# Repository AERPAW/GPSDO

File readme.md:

# AERPAW GPSDO

This repository contains the firmware, host utilities and design files for the AERPAW GPSDO.

The firmware is available in `firmware/` and the status utility in `gpsdo_status/`. See the readme in each for more information.

Install `gpsdo_cli` on Linux:

```sh
curl -fsSL https://raw.githubusercontent.com/AERPAW/GPSDO/main/gpsdo_cli/gpsdo_cli.py | sudo install -m 0755 /dev/stdin /usr/local/bin/gpsdo_cli
```

If `gpsdo_cli` cannot access `/dev/ttyACM*`, add your user to the serial device group and log out/in:

```sh
sudo usermod -aG dialout "$USER"
```

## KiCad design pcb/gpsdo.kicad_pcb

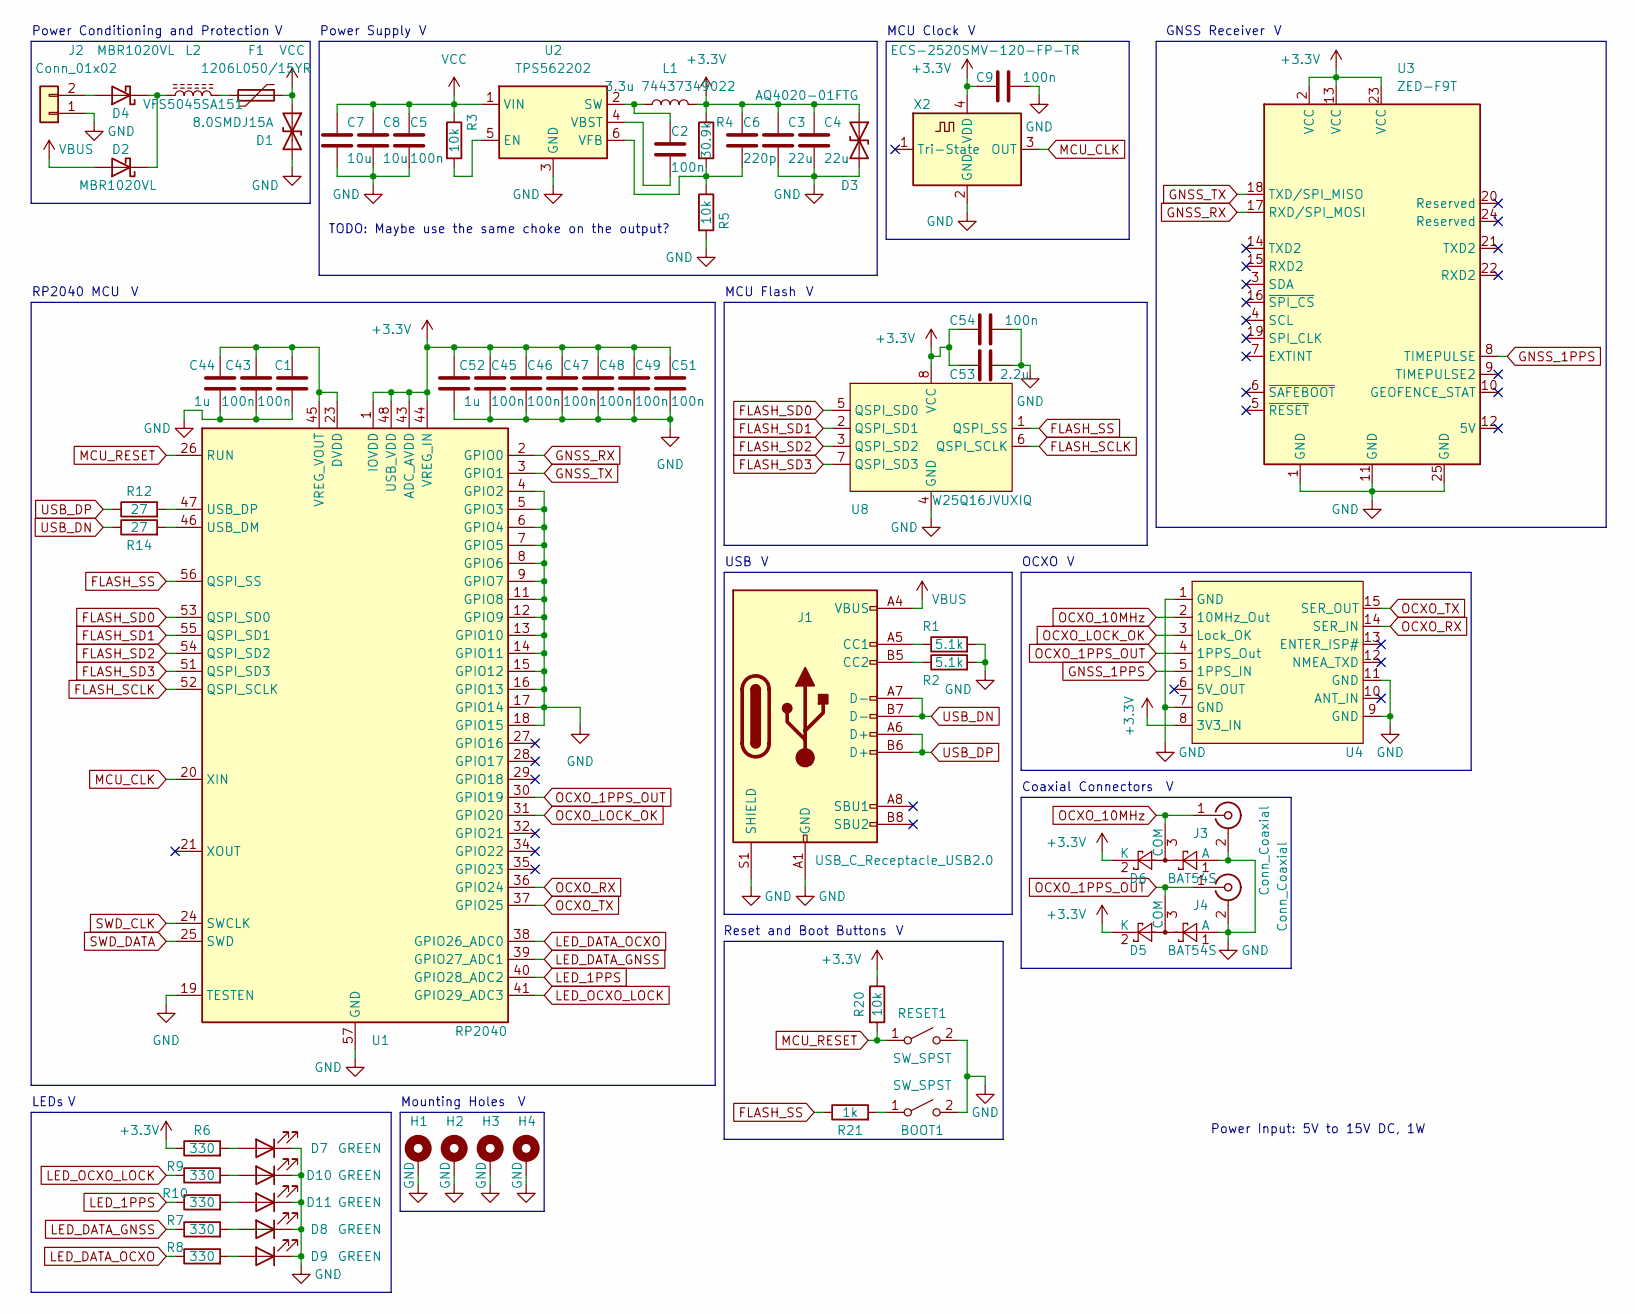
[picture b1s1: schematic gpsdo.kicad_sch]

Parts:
BOOT1: SW_SPST; SW_SPST_B3U-1000P-B
C1, C2, C5, C9, C43, C45, C46, C47, C48, C49, C51, C54: 100n; C_0805_2012Metric_Pad1.18x1.45mm_HandSolder
C3, C4: 22u; C_1210_3225Metric_Pad1.33x2.70mm_HandSolder
C6: 220p; C_0805_2012Metric_Pad1.18x1.45mm_HandSolder
C7, C8: 10u; C_0805_2012Metric_Pad1.18x1.45mm_HandSolder
C44, C52: 1u; C_0805_2012Metric_Pad1.18x1.45mm_HandSolder
C53: 2.2u; C_0805_2012Metric_Pad1.18x1.45mm_HandSolder
D1: 8.0SMDJ15A; D_SMC_Handsoldering
D2, D4: MBR1020VL; D_SOD-123F
D3: AQ4020-01FTG; D_SOD-323_HandSoldering
D5, D6: BAT54S; SOT-23
D7, D8, D9, D10, D11: GREEN; LED_0805_2012Metric_Pad1.15x1.40mm_HandSolder
F1: 1206L050/15YR; Fuse_1206_3216Metric_Pad1.42x1.75mm_HandSolder
H1, H2, H3, H4: MountingHole_Pad; MountingHole_3.2mm_M3_DIN965_Pad
J1: USB_C_Receptacle_USB2.0; USB_C_Receptacle_GCT_USB4105-xx-A_16P_TopMnt_Horizontal
J2: Conn_01x02; CONN_1843790
J3, J4: Conn_Coaxial; TAOGLAS_EMPCB.SMAFSTJ.B.HT
L1: 3.3u 74437349022; 74437349022
L2: VFS5045SA151; L_APV_ANR5045
R1, R2: 5.1k; R_0805_2012Metric_Pad1.20x1.40mm_HandSolder
R3, R5, R20: 10k; R_0805_2012Metric_Pad1.20x1.40mm_HandSolder
R4: 30.9k; R_0805_2012Metric_Pad1.20x1.40mm_HandSolder
R6, R7, R8, R9, R10: 330; R_0805_2012Metric_Pad1.20x1.40mm_HandSolder
R12, R14: 27; R_0805_2012Metric_Pad1.20x1.40mm_HandSolder
R21: 1k; R_0805_2012Metric_Pad1.20x1.40mm_HandSolder
RESET1: SW_SPST; SW_SPST_B3U-1000P-B
U1: RP2040; QFN-56-1EP_7x7mm_P0.4mm_EP3.2x3.2mm
U2: TPS562202; SOT-563
U3: ZED-F9T; MODULE_GPS-15136
U4: 15 Pin GPSDO
U8: W25Q16JVUXIQ; SON50P300X200X60-9N
X2: ECS-2520SMV-120-FP-TR; Oscillator_SMD_ECS_2520MV-xxx-xx-4Pin_2.5x2.0mm

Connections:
+3.3V: C3.1, C4.1, C6.1, C9.1, C45.1, C46.1, C47.1, C48.1, C49.1, C51.1, C52.2, C53.1, C54.1, D3.1 (A1), D5.2 (K), D6.2 (K), L1.2, R4.1, R6.1, R20.1, U1.1 (IOVDD), U1.10 (IOVDD), U1.22 (IOVDD), U1.33 (IOVDD), U1.42 (IOVDD), U1.43 (ADC_AVDD), U1.44 (VREG_IN), U1.48 (USB_VDD), U1.49 (IOVDD), U3.2 (VCC), U3.13 (VCC), U3.23 (VCC), U4.8 (3V3_IN), U8.8 (VCC), X2.4 (VDD)
FLASH_SCLK: U1.52 (QSPI_SCLK), U8.6 (QSPI_SCLK)
FLASH_SD0: U1.53 (QSPI_SD0), U8.5 (QSPI_SD0)
FLASH_SD1: U1.55 (QSPI_SD1), U8.2 (QSPI_SD1)
FLASH_SD2: U1.54 (QSPI_SD2), U8.3 (QSPI_SD2)
FLASH_SD3: U1.51 (QSPI_SD3), U8.7 (QSPI_SD3)
FLASH_SS: R21.1, U1.56 (QSPI_SS), U8.1 (QSPI_SS)
GND: BOOT1.2 (B), C1.1, C3.2, C4.2, C5.2, C7.2, C8.2, C9.2, C43.1, C44.1, C45.2, C46.2, C47.2, C48.2, C49.2, C51.2, C52.1, C53.2, C54.2, D1.2 (A2), D3.2 (A2), D5.1 (A), D6.1 (A), D7.1 (K), D8.1 (K), D9.1 (K), D10.1 (K), D11.1 (K), H1.1, H2.1, H3.1, H4.1, J1.A1 (GND), J1.A12 (GND), J1.B1 (GND), J1.B12 (GND), J1.S1 (SHIELD), J2.1, J3.2 (Ext), J4.2 (Ext), R1.2, R2.2, R5.2, RESET1.2 (B), U1.4 (GPIO2), U1.5 (GPIO3), U1.6 (GPIO4), U1.7 (GPIO5), U1.8 (GPIO6), U1.9 (GPIO7), U1.11 (GPIO8), U1.12 (GPIO9), U1.13 (GPIO10), U1.14 (GPIO11), U1.15 (GPIO12), U1.16 (GPIO13), U1.17 (GPIO14), U1.18 (GPIO15), U1.19 (TESTEN), U1.57 (GND), U2.3 (GND), U3.1 (GND), U3.11 (GND), U3.25 (GND), U4.1 (GND), U4.7 (GND), U4.9 (GND), U4.11 (GND), U8.4 (GND), X2.2 (GND)
GNSS_1PPS: U3.8 (TIMEPULSE), U4.5 (1PPS_IN)
GNSS_RX: U1.2 (GPIO0), U3.17 (RXD/SPI_MOSI)
GNSS_TX: U1.3 (GPIO1), U3.18 (TXD/SPI_MISO)
LED_1PPS: R10.1, U1.40 (GPIO28_ADC2)
LED_DATA_GNSS: R7.1, U1.39 (GPIO27_ADC1)
LED_DATA_OCXO: R8.1, U1.38 (GPIO26_ADC0)
LED_OCXO_LOCK: R9.1, U1.41 (GPIO29_ADC3)
MCU_CLK: U1.20 (XIN), X2.3 (OUT)
MCU_RESET: R20.2, RESET1.1 (A), U1.26 (RUN)
unnamed: BOOT1.1 (A), R21.2
unnamed: D2.1 (K), D4.1 (K), L2.1
unnamed: D4.2 (A), J2.2
unnamed: D7.2 (A), R6.2
unnamed: D8.2 (A), R7.2
unnamed: D9.2 (A), R8.2
unnamed: D10.2 (A), R9.2
unnamed: D11.2 (A), R10.2
unnamed: F1.1, L2.2
unnamed: J1.A5 (CC1), R1.1
unnamed: J1.B5 (CC2), R2.1
unnamed: R14.2, U1.46 (USB_DM)
unnamed: R12.2, U1.47 (USB_DP)
unnamed: C1.2, C43.2, C44.2, U1.23 (DVDD), U1.45 (VREG_VOUT), U1.50 (DVDD)
unnamed: R3.2, U2.5 (EN)
unnamed: C2.1, L1.1, U2.2 (SW)
unnamed: C2.2, U2.4 (VBST)
unnamed: C6.2, R4.2, R5.1, U2.6 (VFB)
OCXO_1PPS_OUT: D5.3 (COM), J4.1 (In), U1.30 (GPIO19), U4.4 (1PPS_Out)
OCXO_10MHz: D6.3 (COM), J3.1 (In), U4.2 (10MHz_Out)
OCXO_LOCK_OK: U1.31 (GPIO20), U4.3 (Lock_OK)
OCXO_RX: U1.36 (GPIO24), U4.14 (SER_IN)
OCXO_TX: U1.37 (GPIO25), U4.15 (SER_OUT)
SWD_CLK: U1.24 (SWCLK)
SWD_DATA: U1.25 (SWD)
USB_DN: J1.A7 (D-), J1.B7 (D-), R14.1
USB_DP: J1.A6 (D+), J1.B6 (D+), R12.1
VBUS: D2.2 (A), J1.A4 (VBUS), J1.A9 (VBUS), J1.B4 (VBUS), J1.B9 (VBUS)
VCC: C5.1, C7.1, C8.1, D1.1 (A1), F1.2, R3.1, U2.1 (VIN)

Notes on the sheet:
Reset and Boot Buttons
Power Conditioning and Protection
Power Supply
LEDs
Mounting Holes
Coaxial Connectors
RP2040 MCU
MCU Flash
Power Input: 5V to 15V DC, 1W
TODO: Maybe use the same choke on the output?
OCXO
USB
MCU Clock
GNSS Receiver

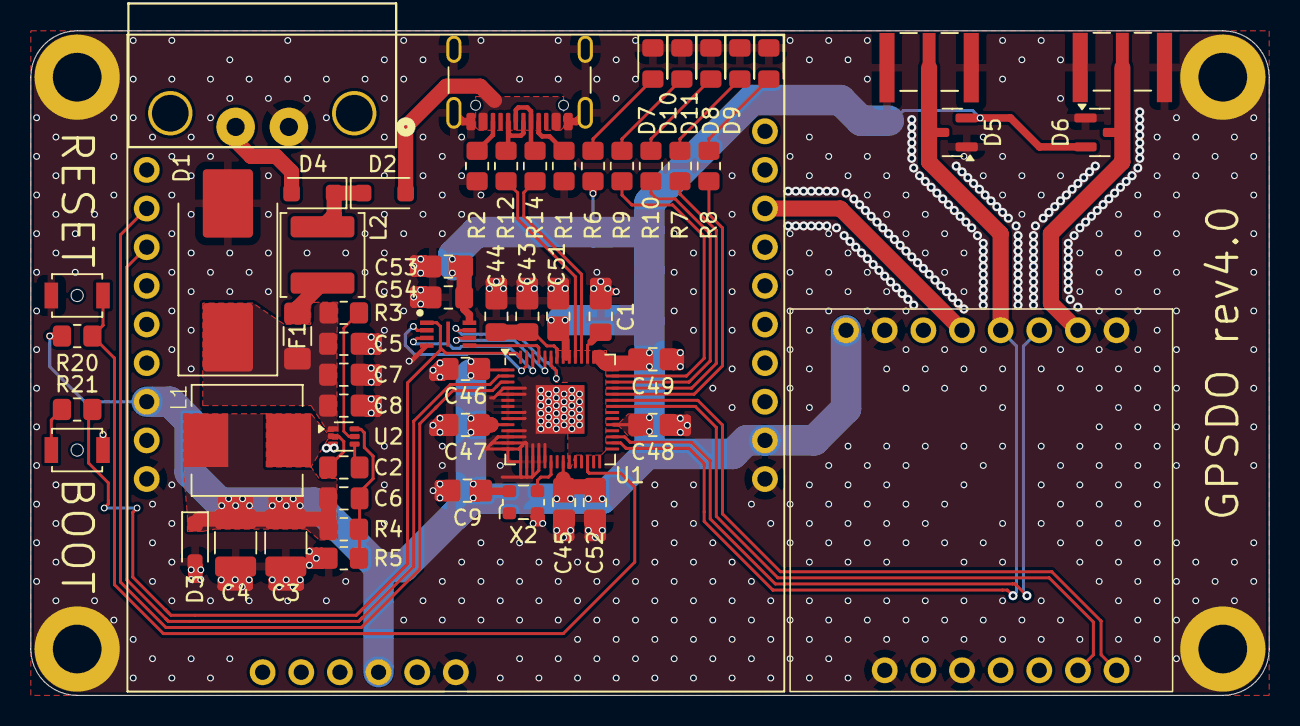
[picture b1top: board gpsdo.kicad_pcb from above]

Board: 2 copper layers, 81.4 x 43.7 mm, 64 parts (0 on the bottom side), 44 nets.

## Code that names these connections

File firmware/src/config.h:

#pragma once
#include <hardware/uart.h>

#define GNSS_CDC_IFACE      0
#define GNSS_UART           uart0
#define GNSS_TX_PIN         0
#define GNSS_RX_PIN         1
#define GNSS_DATA_LED_PIN   27

#define OCXO_CDC_IFACE      1
#define OCXO_UART           uart1
#define OCXO_TX_PIN         24
#define OCXO_RX_PIN         25
#define OCXO_1PPS_PIN       19
#define OCXO_LOCK_PIN       20
#define OCXO_DATA_LED_PIN   26
#define OCXO_1PPS_LED_PIN   28
#define OCXO_LOCK_LED_PIN   29


// Note: this is set to avoid uart writes taking too long
#define DEFAULT_GNSS_BAUDRATE   38400
#define DEFAULT_OCXO_BAUDRATE   115200
#define BUFFER_SIZE             64

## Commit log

2026-03-06 Add zed f9t ubx config
2026-03-06 Add gpsdo_cli
2026-05-11 Add instructions for installation
